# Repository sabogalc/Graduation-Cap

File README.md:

# Graduation Cap
This is a PCB that I made to sit on top of my graduation cap for my bachelor's in electrical engineering. The board is designed around the 9.5x9.5" Herff Jones caps used at UF, but it could easily be adapted for other caps. This board is capable of playing three different `.WAV` music files, and I have populated mine with three Florida Gators fight songs. There is also an LED sequence that cycles through each light on the cap while displaying a message on the OLED display.

> 
> Side-by-side of the PCB render in KiCad and the board on my cap in real life.

# Project Inspirations

While I have had this project on my mind for a few years now, there are some people that have made similar projects, and I modeled some of my work off of theirs.

1. [LED Graduation Cap](https://github.com/matthewScohen/LED_Graduation_Cap) by Matthew Cohen

2. [Graduation Cap](https://github.com/miekush/graduation-cap) by Mike Kushnerik

Notably, Mike's project has accommodations for the tassel, which I overlooked and ended up just hot gluing onto my cap. The PCB itself is also hot glued at each of the cap's four corners.

# Code

The program to run this board is included in this repository as `main.py`, and it was designed around a Raspberry Pi Pico running MicroPython (yes, I know C would have run better, no I am not good at writing code). You will need the following driver files saved to the Pico in order for the code to run.

1. [sdcard.py](https://github.com/micropython/micropython-lib/blob/master/micropython/drivers/storage/sdcard/sdcard.py) from [micropython-lib](https://github.com/micropython/micropython-lib)

2. [sh1106.py](https://github.com/raspberrypi/pico-micropython-examples/blob/master/i2c/1106oled/sh1106.py) from [Pico MicroPython Examples](https://github.com/raspberrypi/pico-micropython-examples)

3. [tlc5940.py](https://github.com/sabogalc/tlc5940-micropython/blob/master/tlc5940.py) from [TLC5940 MicroPython Library](https://github.com/oysols/tlc5940-micropython)**

** **Please note that the code does not currently work on the Pico. I have linked to my fork of the driver which does work on the Pico and has been submitted as a pull request.**

4. [wavplayer.py](https://github.com/miketeachman/micropython-i2s-examples/blob/master/examples/wavplayer.py) from [MicroPython I2S Examples](https://github.com/miketeachman/micropython-i2s-examples)

# Ordering Parts

I have included BOMs for both DigiKey and Mouser to obtain the parts for this board, but the Mouser BOM is missing the socket headers since I could not find any on there. The board will still work with the components directly soldered down, but I liked the flexibility the sockets offered, especially while debugging. One component that will be needed to be purchased externally is the I2C OLED, and I got mine [on Amazon](https://www.amazon.com/dp/B07BHHV844).

# Notes

I wanted to have a mode where all the lights could come on at once, but I was unable to accomplish this without prominent flickering. I believe this may be due to differences in the forward voltages of the blue and orange LEDs, as the flicker does not occur when only lighting multiple LEDs of one color (side note, the blue LED was [partially invented at UF](https://www.nobelprize.org/prizes/physics/2014/nakamura/biographical/#:~:text=In%20March%201988%20Shuji%20flew%20to%20Gainesville.%20It%20was%20the%20first%20time%20the%20country%20boy%20had%20boarded%20an%20airplane.%20Like%20many%20first%2Dtime%20fliers%2C%20he%20feared%20it%20might%20fall%20from%20the%20sky.%20It%20was%20also%20his%20first%20trip%20abroad.%20He%20worried%20that%20his%20rudimentary%20English%20would%20not%20enable%20him%20to%20communicate%20with%20Americans.)!). If anyone has more information on this, please feel free to share it.

Another thing to note is that I had to cut a hole in my cap so that the battery leads were accessible, but if you wanted to power the board with a USB cable and a power bank that should work as well.

While the board is personalized to me and my graduation year, it can be modified to any year, school, or person. Of course, most of the fun in making something like this is in designing it yourself, so feel free to use this project in part or in whole to help move your project along.

> 
> Me with my graduation cap outside of UF's New Engineering Building (it's not that new but the name has stuck).

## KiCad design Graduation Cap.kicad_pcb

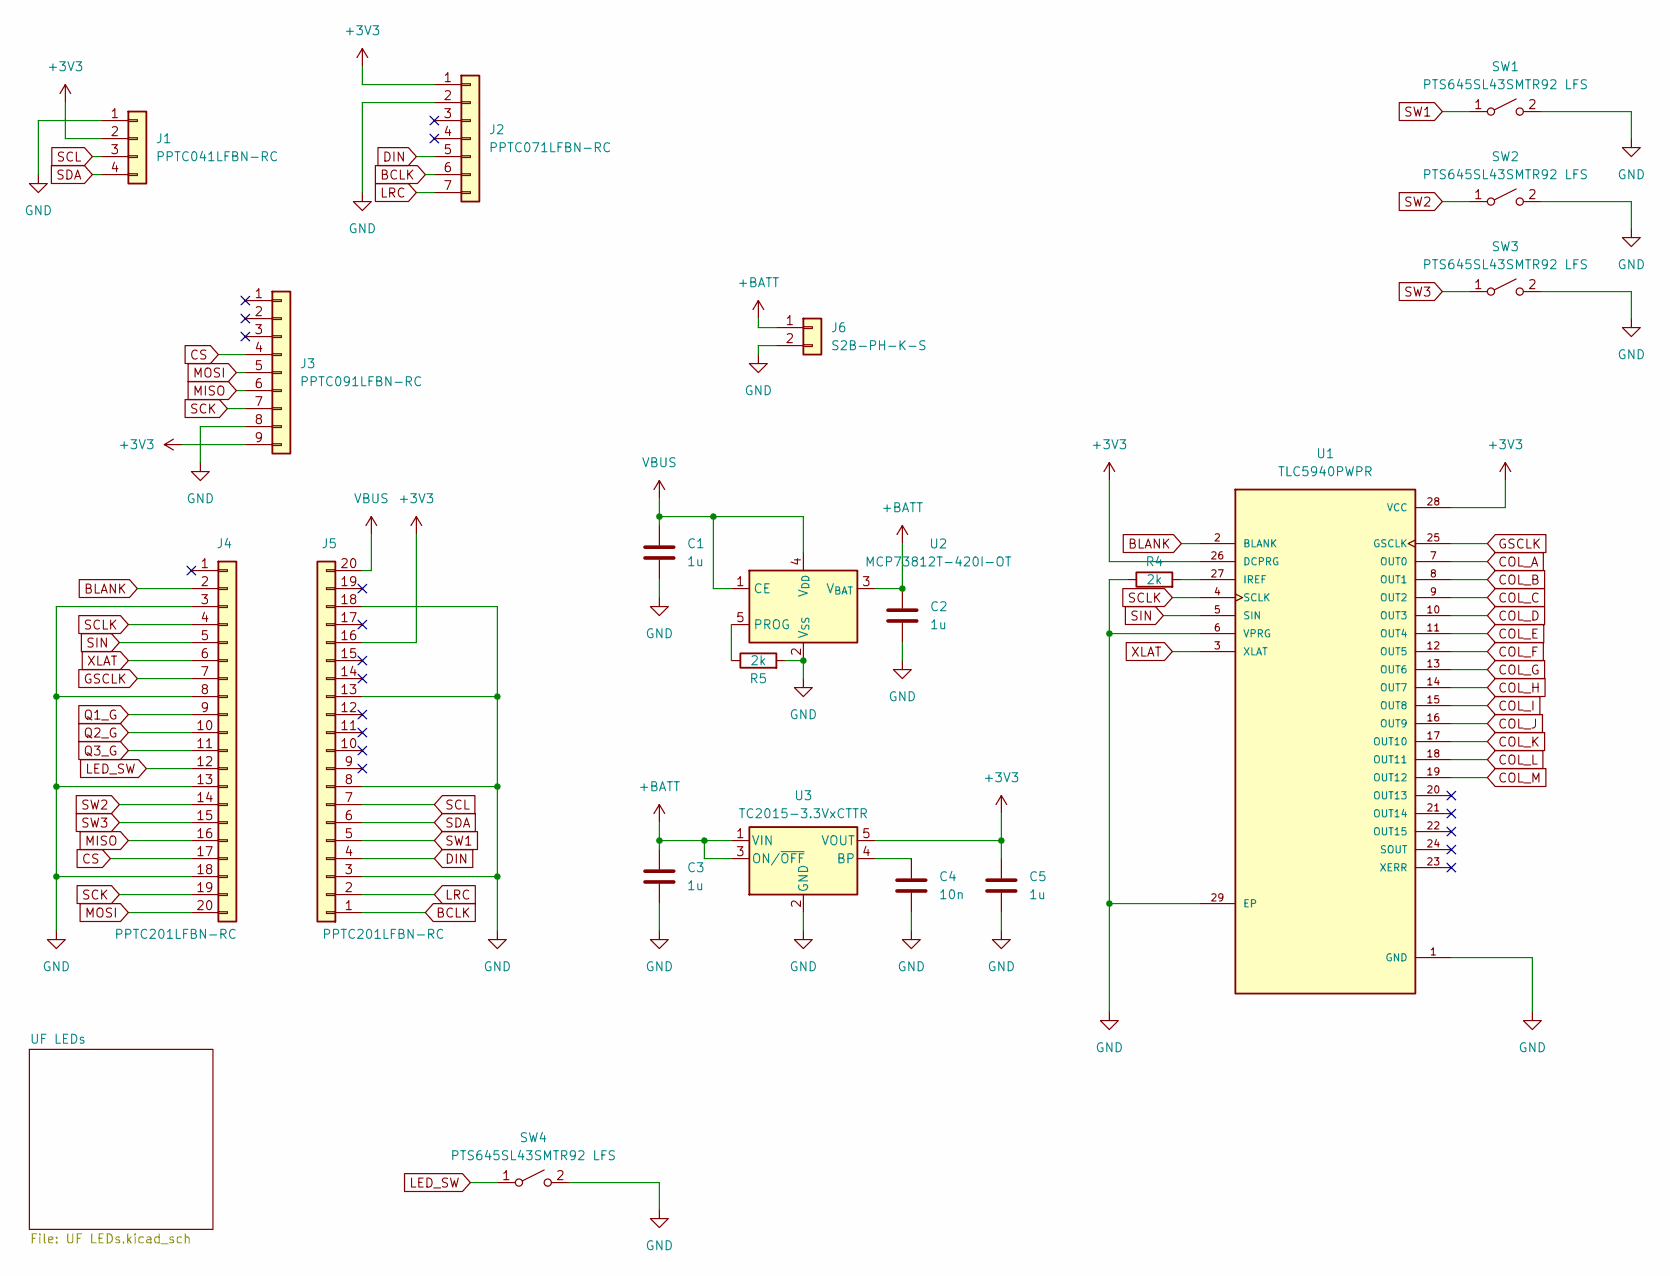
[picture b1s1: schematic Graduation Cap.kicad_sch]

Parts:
C1, C2, C3, C5: 1u; C_0603_1608Metric
C4: 10n; C_0603_1608Metric
J1: PPTC041LFBN-RC; PinSocket_1x04_P2.54mm_Vertical
J2: PPTC071LFBN-RC; PinSocket_1x07_P2.54mm_Vertical
J3: PPTC091LFBN-RC; PinSocket_1x09_P2.54mm_Vertical
J4, J5: PPTC201LFBN-RC; PinSocket_1x20_P2.54mm_Vertical
J6: S2B-PH-K-S; JST_PH_S2B-PH-K_1x02_P2.00mm_Horizontal
R4, R5: 2k; R_0603_1608Metric
SW1, SW2, SW3, SW4: PTS645SL43SMTR92 LFS; SW_SPST_PTS645
U1: TLC5940PWPR; HTSSOP-28-1EP_4.4x9.7mm_P0.65mm_EP3.4x9.5mm_Mask2.4x6.17mm_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
U2: MCP73812T-420I-OT; SOT-23-5
U3: TC2015-3.3VxCTTR; SOT-23-5

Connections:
+3V3: C5.1, J1.2, J2.1, J3.9, J5.16, U1.26 (DCPRG), U1.28 (VCC), U3.5 (VOUT); also elsewhere on the board
+BATT: C2.1, C3.1, J6.1, U2.3 (V_{BAT}), U3.1 (VIN), U3.3 (ON/~OFF)
BCLK: J2.6, J5.1
BLANK: J4.2, U1.2 (BLANK)
COL_A: U1.7 (OUT0); also elsewhere on the board
COL_B: U1.8 (OUT1); also elsewhere on the board
COL_C: U1.9 (OUT2); also elsewhere on the board
COL_D: U1.10 (OUT3); also elsewhere on the board
COL_E: U1.11 (OUT4); also elsewhere on the board
COL_F: U1.12 (OUT5); also elsewhere on the board
COL_G: U1.13 (OUT6); also elsewhere on the board
COL_H: U1.14 (OUT7); also elsewhere on the board
COL_I: U1.15 (OUT8); also elsewhere on the board
COL_J: U1.16 (OUT9); also elsewhere on the board
COL_K: U1.17 (OUT10); also elsewhere on the board
COL_L: U1.18 (OUT11); also elsewhere on the board
COL_M: U1.19 (OUT12); also elsewhere on the board
CS: J3.4, J4.17
DIN: J2.5, J5.4
GND: C1.2, C2.2, C3.2, C4.2, C5.2, J1.1, J2.2, J3.8, J4.3, J4.8, J4.13, J4.18, J5.3, J5.8, J5.13, J5.18, J6.2, R4.1, R5.2, SW1.2 (B), SW2.2 (B), SW3.2 (B), SW4.2 (B), U1.1 (GND), U1.6 (VPRG), U1.29 (EP), U2.2 (V_{SS}), U3.2 (GND)
GSCLK: J4.7, U1.25 (GSCLK)
LED_SW: J4.12, SW4.1 (A)
LRC: J2.7, J5.2
MISO: J3.6, J4.16
MOSI: J3.5, J4.20
unnamed: R4.2, U1.27 (IREF)
unnamed: R5.1, U2.5 (PROG)
unnamed: C4.1, U3.4 (BP)
Q1_G: J4.9; also elsewhere on the board
Q2_G: J4.10; also elsewhere on the board
Q3_G: J4.11; also elsewhere on the board
SCK: J3.7, J4.19
SCL: J1.3, J5.7
SCLK: J4.4, U1.4 (SCLK)
SDA: J1.4, J5.6
SIN: J4.5, U1.5 (SIN)
SW1: J5.5, SW1.1 (A)
SW2: J4.14, SW2.1 (A)
SW3: J4.15, SW3.1 (A)
VBUS: C1.1, J5.20, U2.1 (CE), U2.4 (V_{DD})
XLAT: J4.6, U1.3 (XLAT)

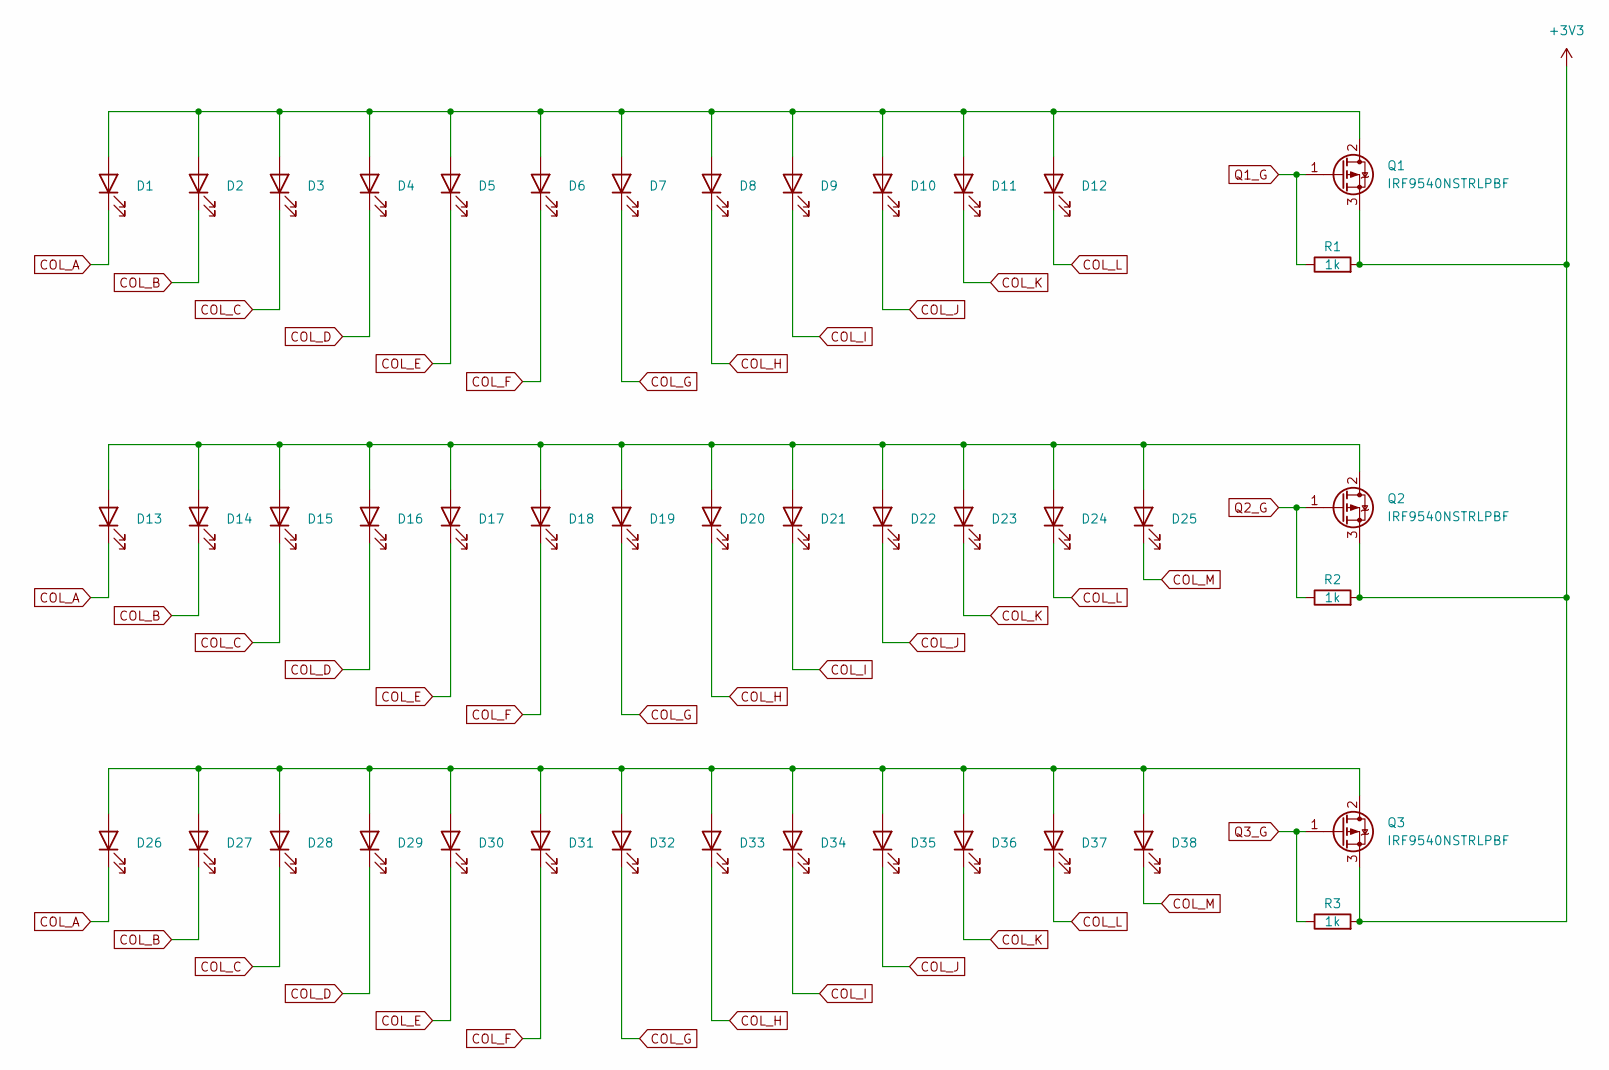
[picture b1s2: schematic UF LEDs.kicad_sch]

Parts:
D1, D2, D3, D4, D5, D6, D7, D8, D9, D10, D11, D12, D13, D14, D15, D16, D17, D18: 151051BS04000; BLUE-LED-5MM-ROUND
D19, D20, D21, D22, D23, D24, D25, D26, D27, D28, D29, D30, D31, D32, D33, D34, D35, D36, D37, D38: SLI-343D8U3F; ORANGE-LED-5MM-ROUND
Q1, Q2, Q3: IRF9540NSTRLPBF; TO-263-2
R1, R2, R3: 1k; R_0603_1608Metric

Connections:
+3V3: Q1.3 (S), Q2.3 (S), Q3.3 (S), R1.2, R2.2, R3.2; also elsewhere on the board
COL_A: D1.1 (K), D13.1 (K), D26.1 (K); also elsewhere on the board
COL_B: D2.1 (K), D14.1 (K), D27.1 (K); also elsewhere on the board
COL_C: D3.1 (K), D15.1 (K), D28.1 (K); also elsewhere on the board
COL_D: D4.1 (K), D16.1 (K), D29.1 (K); also elsewhere on the board
COL_E: D5.1 (K), D17.1 (K), D30.1 (K); also elsewhere on the board
COL_F: D6.1 (K), D18.1 (K), D31.1 (K); also elsewhere on the board
COL_G: D7.1 (K), D19.1 (K), D32.1 (K); also elsewhere on the board
COL_H: D8.1 (K), D20.1 (K), D33.1 (K); also elsewhere on the board
COL_I: D9.1 (K), D21.1 (K), D34.1 (K); also elsewhere on the board
COL_J: D10.1 (K), D22.1 (K), D35.1 (K); also elsewhere on the board
COL_K: D11.1 (K), D23.1 (K), D36.1 (K); also elsewhere on the board
COL_L: D12.1 (K), D24.1 (K), D37.1 (K); also elsewhere on the board
COL_M: D25.1 (K), D38.1 (K); also elsewhere on the board
unnamed: D1.2 (A), D2.2 (A), D3.2 (A), D4.2 (A), D5.2 (A), D6.2 (A), D7.2 (A), D8.2 (A), D9.2 (A), D10.2 (A), D11.2 (A), D12.2 (A), Q1.2 (D)
unnamed: D13.2 (A), D14.2 (A), D15.2 (A), D16.2 (A), D17.2 (A), D18.2 (A), D19.2 (A), D20.2 (A), D21.2 (A), D22.2 (A), D23.2 (A), D24.2 (A), D25.2 (A), Q2.2 (D)
unnamed: D26.2 (A), D27.2 (A), D28.2 (A), D29.2 (A), D30.2 (A), D31.2 (A), D32.2 (A), D33.2 (A), D34.2 (A), D35.2 (A), D36.2 (A), D37.2 (A), D38.2 (A), Q3.2 (D)
Q1_G: Q1.1 (G), R1.1; also elsewhere on the board
Q2_G: Q2.1 (G), R2.1; also elsewhere on the board
Q3_G: Q3.1 (G), R3.1; also elsewhere on the board

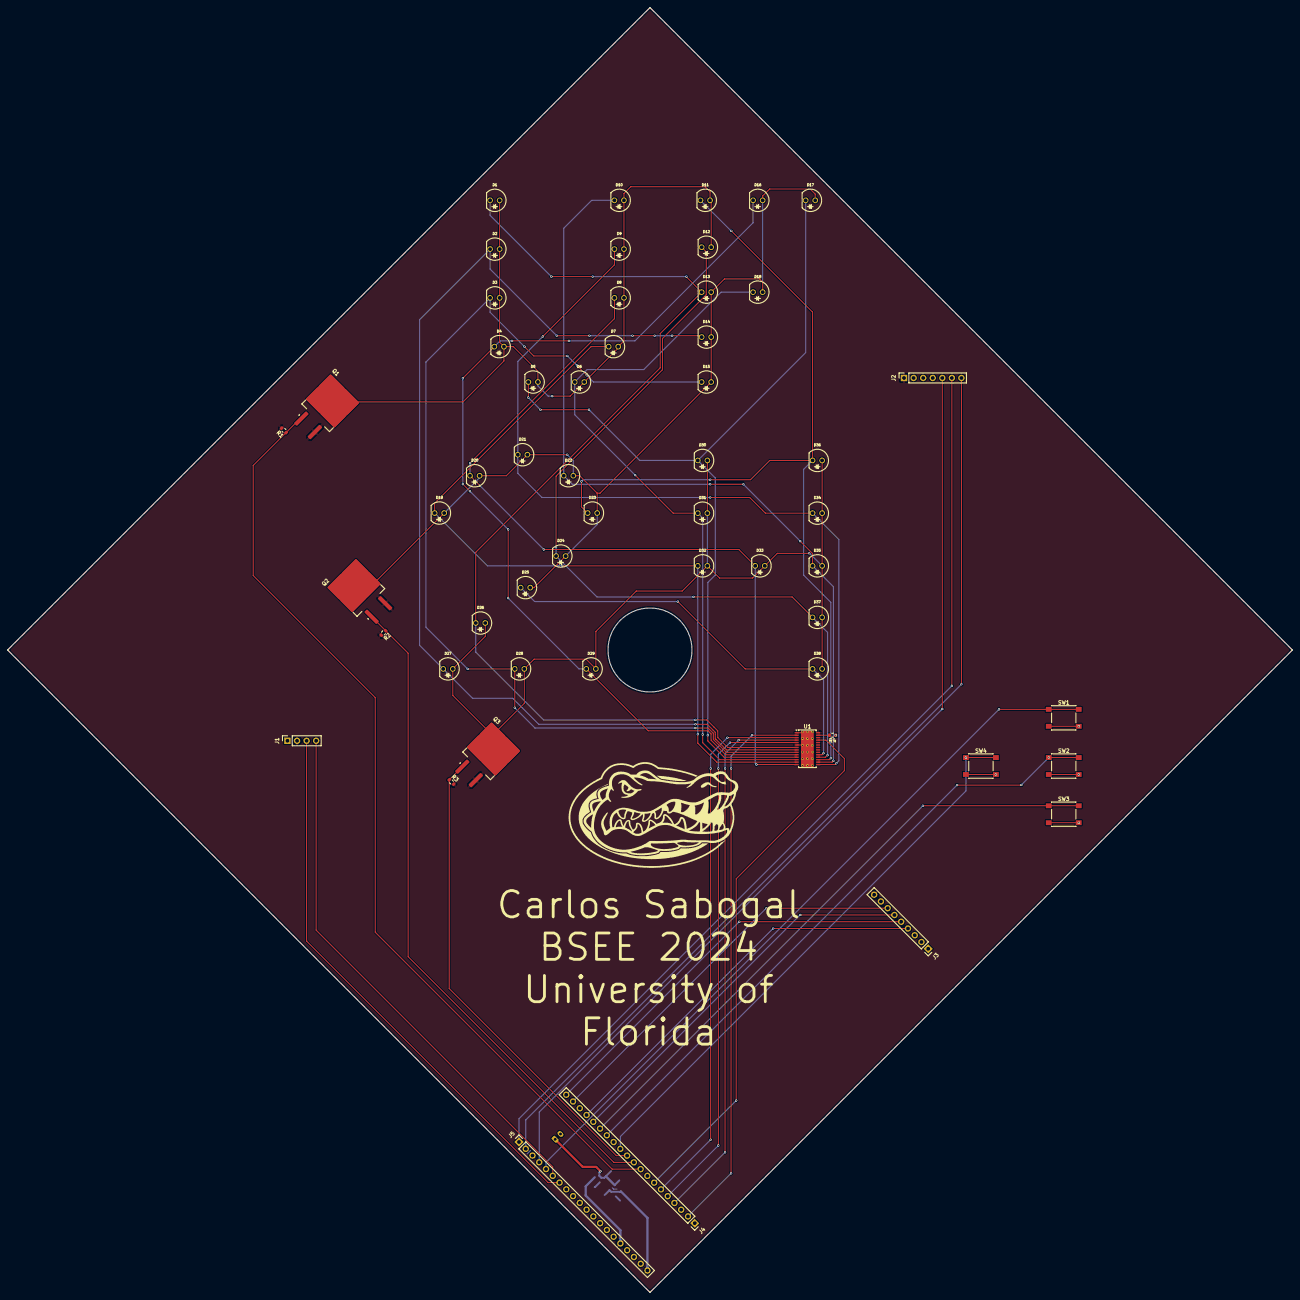
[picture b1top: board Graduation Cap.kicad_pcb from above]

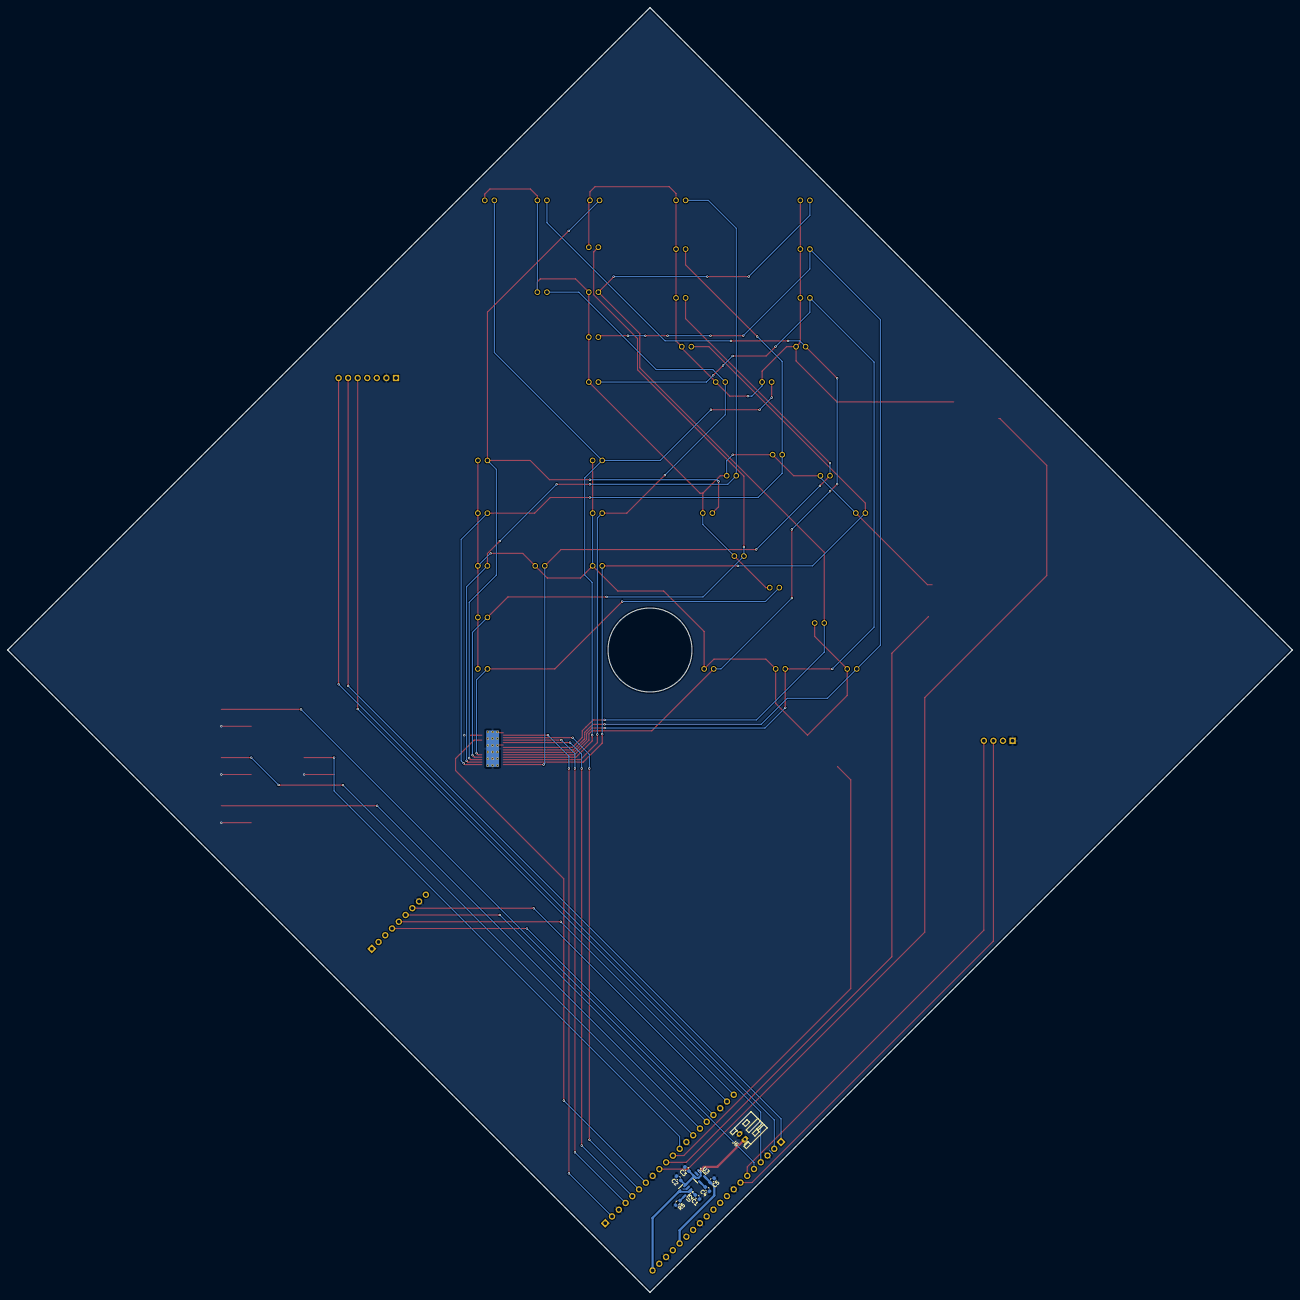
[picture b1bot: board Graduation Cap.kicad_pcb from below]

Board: 2 copper layers, 341.2 x 341.2 mm, 64 parts (9 on the bottom side), 44 nets.

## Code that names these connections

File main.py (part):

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from tlc5940 import interface, simple_byte_array

# TLC5940 GPIO pin definitions
GSCLK_PIN = 5
BLANK_PIN = 1
VPRG_PIN = 0
XLAT_PIN = 4
SCLK_PIN = 2
SIN_PIN = 3

# PMOS gate pins
PMOS_ROW1_PIN = 7
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PMOS_ROW3_PIN = 8

# Initialize the TLC5940 interface
tlc = interface(GSCLK_PIN, BLANK_PIN, VPRG_PIN, XLAT_PIN, SCLK_PIN, SIN_PIN)

# Configure PMOS pins
pmos_row1 = Pin(PMOS_ROW1_PIN, Pin.OUT)
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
